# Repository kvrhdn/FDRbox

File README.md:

FDRbox
===
By Koenraad Verheyden - [@koenaad](https://twitter.com/koenaad)

Description
---
A simple USB MIDI controller with 8 faders.

[Album with images](http://imgur.com/a/iQqRE)

Status
---
I assembled a couple of boards and __they all work completely__!

TODO
* finish off design: find fadercaps, some screws and feet.
* clean up code.

Code
---
[```code/```](code/) is a subtree of [PIC16F145x_MIDI](https://github.com/koenaad/PIC16F145x_MIDI). The application specific code is in [```main.c```](code/main.c).

This project uses the USB stack from [Microchip Libraries for Applications](http://microchip.com/mla).  
MLA is licensed under the Apache License version 2.0. (See: [microchip.com/mla_license](http://microchip.com/mla_license))

PCB
---
[```pcb/```](pcb/) contains the schematics and design of the PCB. The entire PCB was designed using [KiCad](http://kicad-pcb.org/), an open-source software suite for EDA.

PDF's of the schematic are placed in [```pcb/output/```](pcb/output/).  
You can find the Gerber files I used here: [```pcb/output/FDRbox_v0.1_gerber/```](pcb/output/FDRbox_v0.1_gerber/)

Frontpanel
---
I also designed a frontpanel, [```frontpanel```](frontpanel/) contains the SVG I used to lasercut it.

Ableton Live MIDI Remote Script
---
[```Ableton Live MIDI Remote Script/```](Ableton Live MIDI Remote Script/) contains a MIDI Remote Script for Ableton Live. The script maps the faders to control the volume of the first 8 tracks.  
Using this script is not necessary to use FDRbox in Live (or any other DAW that supports MIDI controllers), all it does is automatically map the controls for you.

To install the script, please refer to [ableton.com: How to install a third-party Remote Script?
](https://www.ableton.com/en/help/article/install-third-party-remote-script/)

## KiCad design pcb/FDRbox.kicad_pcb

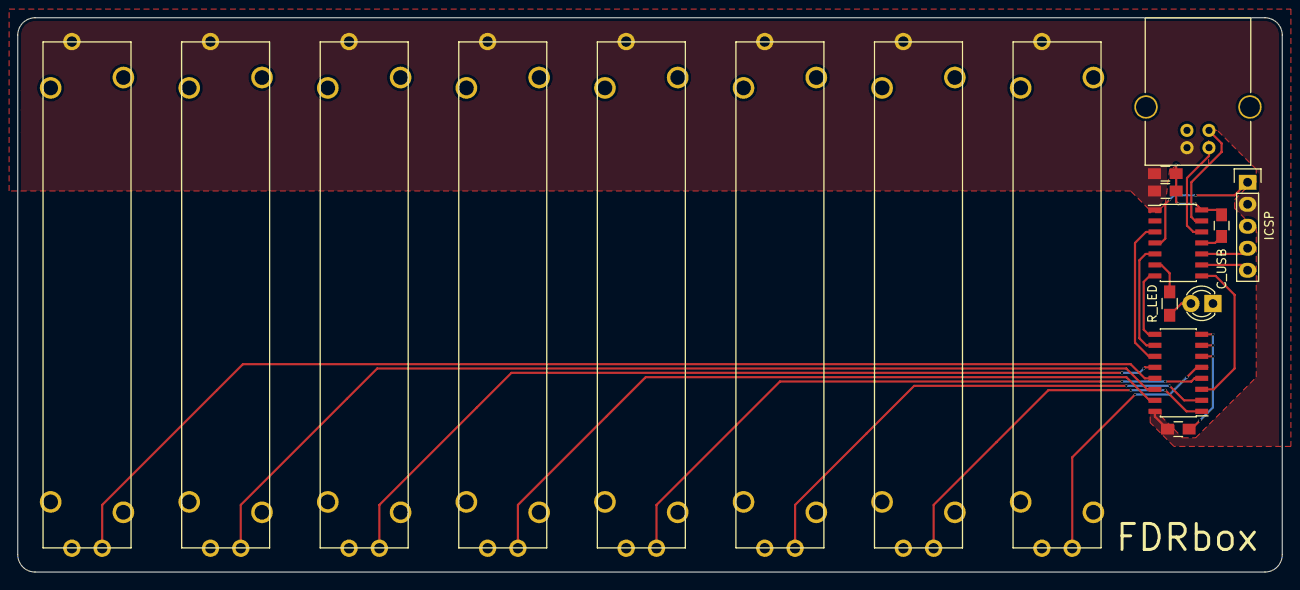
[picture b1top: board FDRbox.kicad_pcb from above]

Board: 2 copper layers, 146.0 x 64.0 mm, 18 parts (0 on the bottom side), 22 nets.

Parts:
C1, C2: 100nF; C_0805_HandSoldering
C3: 1µF; C_0805_HandSoldering
C_USB: 470nF; C_0805_HandSoldering
D1: LED; LED-3MM
P1: USB_B
P2: ICSP; Pin_Header_Straight_1x05
RV1, RV2, RV3, RV4, RV5, RV6, RV7, RV8: 10k; PTA4543
R_LED: 150Ω; R_0805_HandSoldering
U1: PIC16F1455; SOIC-14_3.9x8.7mm_Pitch1.27mm
U2: 4051; SOIC-16_3.9x9.9mm_Pitch1.27mm

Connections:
+5V: C1.2, C2.2, C3.2, P1.1, P2.2, RV1.3, RV2.3, RV3.3, RV4.3, RV5.3, RV6.3, RV7.3, RV8.3, U1.1, U2.16
/CH_0: U1.3, U2.11
/CH_1: U1.5, U2.10
/CH_2: U1.7, U2.9
/D+: P1.3, U1.13
/D-: P1.2, U1.12
/FDR_0: RV1.2, U2.13
/FDR_1: RV2.2, U2.14
/FDR_2: RV3.2, U2.12
/FDR_3: RV4.2, U2.15
/FDR_4: RV5.2, U2.4
/FDR_5: RV6.2, U2.2
/FDR_6: RV7.2, U2.1
/FDR_7: RV8.2, U2.5
/FDR_X: U1.8, U2.3
/MCLR: P2.1, U1.4
/RC0: P2.4, U1.10
/RC1: P2.5, U1.9
GND: C1.1, C2.1, C3.1, C_USB.1, D1.1, P1.4, P2.3, RV1.1, RV2.1, RV3.1, RV4.1, RV5.1, RV6.1, RV7.1, RV8.1, U1.14, U2.6, U2.7, U2.8
unnamed: C_USB.2, U1.11
unnamed: D1.2, R_LED.2
unnamed: R_LED.1, U1.6

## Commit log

2016-08-07 First long overdue commit.
2016-08-07 Added .editorconfig to force 4 tab width
2016-08-08 Added README.md
2016-08-08 Fixed Imgur album URL
2016-08-08 Fixed some typo's
2016-08-08 Added .gitignore
2016-08-12 Added README
2016-08-12 Edited README concerning subtree
2016-08-12 I/O shouldn't default to analog in
2016-08-12 Implemented reading analog in + filtering
2016-08-12 Added schematic and PCB
2016-08-13 Squashed 'code/' changes from 8bdaec6..a0b4bef
    a0b4bef Switched LED to Timer2
    d4cd9b9 Update led.c to avoid blinking like a fool when a lot of data was sent/received
    cb998f3 I/O shouldn't default to analog in
    git-subtree-dir: code
    git-subtree-split: a0b4bef0063eeb04de062623f3766dd7959061c3
2016-08-13 Started implementing switching MUX channels + organizing
2016-08-15 Implemented switching channels
2016-08-16 Added note to PCB schematic
2016-08-16 Minor changes + clean up
2016-08-16 Updated USB product descriptor
2016-08-26 MPLAB little change in configuration.xml
2016-08-26 Added Ableton Live MIDI Remote Script
2016-08-26 MIDI Remote Script little cleanup
2016-08-26 Updated README with info MIDI Remote Script
2016-08-26 README added info PCB
2016-08-26 README some typo's
2016-08-26 Clean up LED main.c
2016-08-26 Finished samples techniques - implemented double filtering technique
2016-08-26 Cleanup main.c
2016-08-27 Tweaked README
2016-08-30 First sketch frontpanel
2016-09-01 Switch to XC8 1.38
2016-09-01 Added TODO USB VID and PID
2016-09-01 Added output files PCB
2016-09-01 Added link to PDF schematic in README
2016-10-19 Replaced SVG with tested version
2016-10-30 Updated README to reflect currect project status
2016-10-30 Cleaned up code a bit
2016-10-30 Added MIT License
